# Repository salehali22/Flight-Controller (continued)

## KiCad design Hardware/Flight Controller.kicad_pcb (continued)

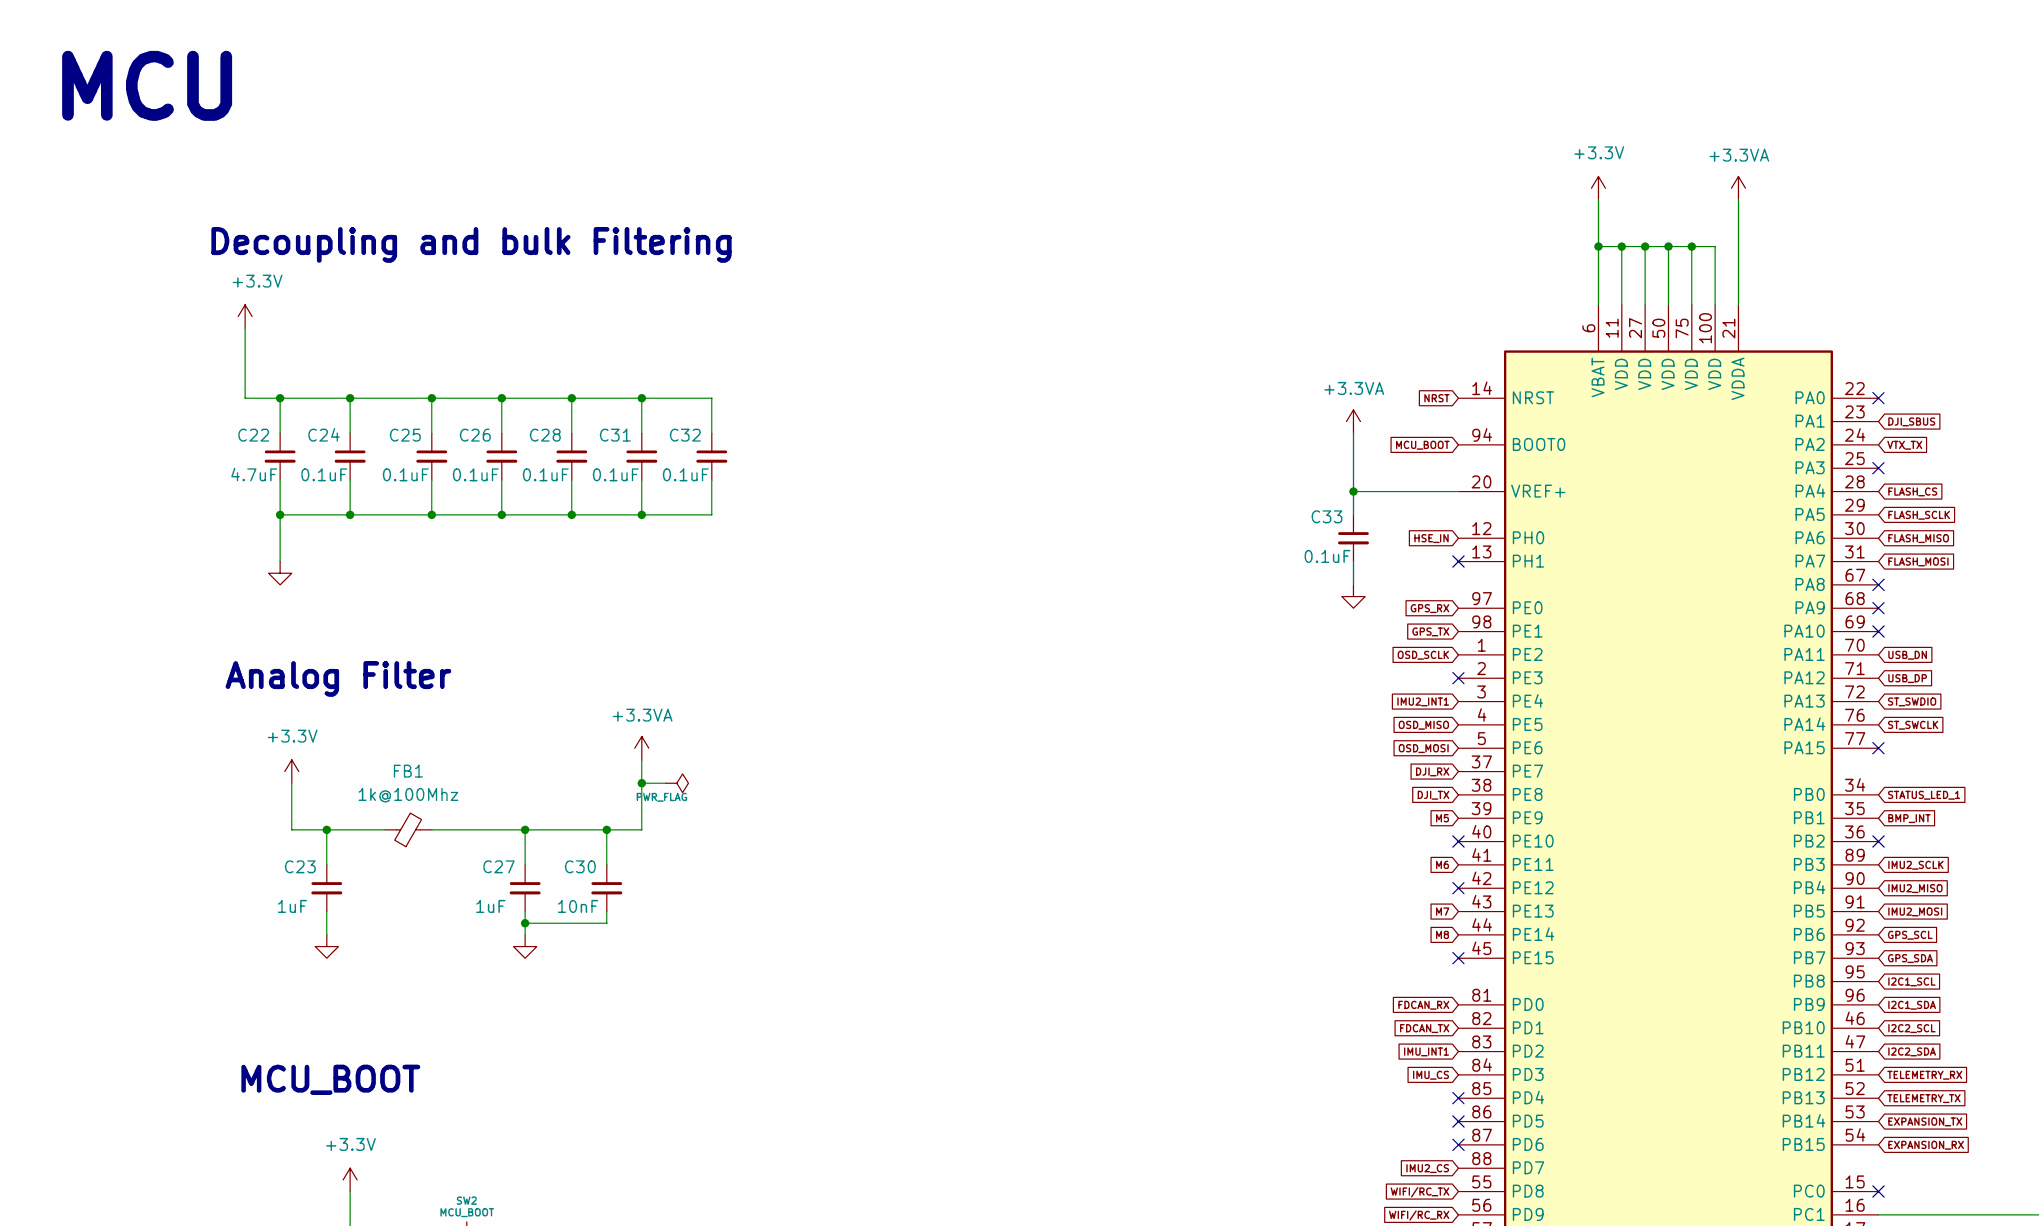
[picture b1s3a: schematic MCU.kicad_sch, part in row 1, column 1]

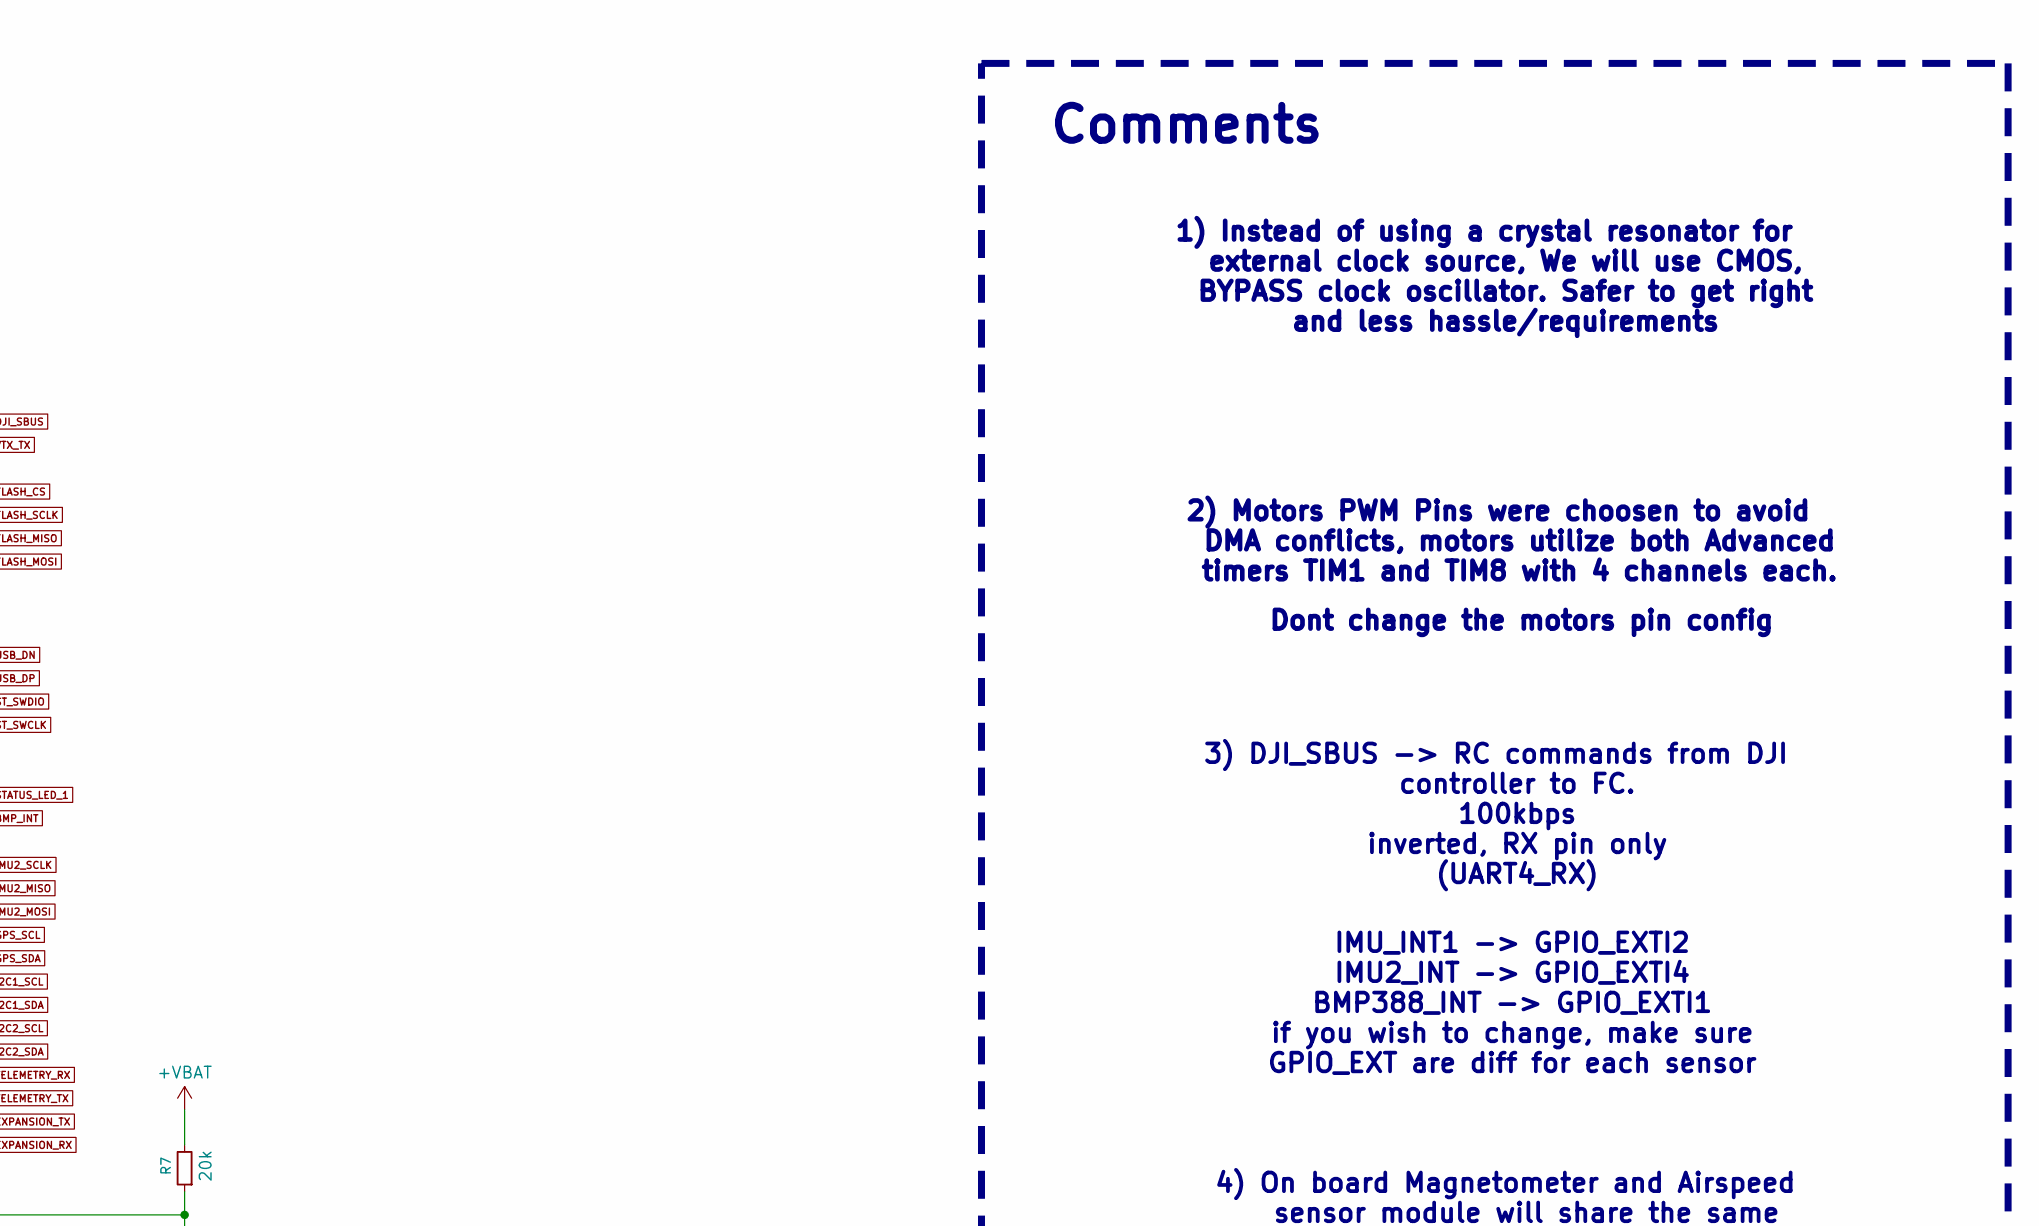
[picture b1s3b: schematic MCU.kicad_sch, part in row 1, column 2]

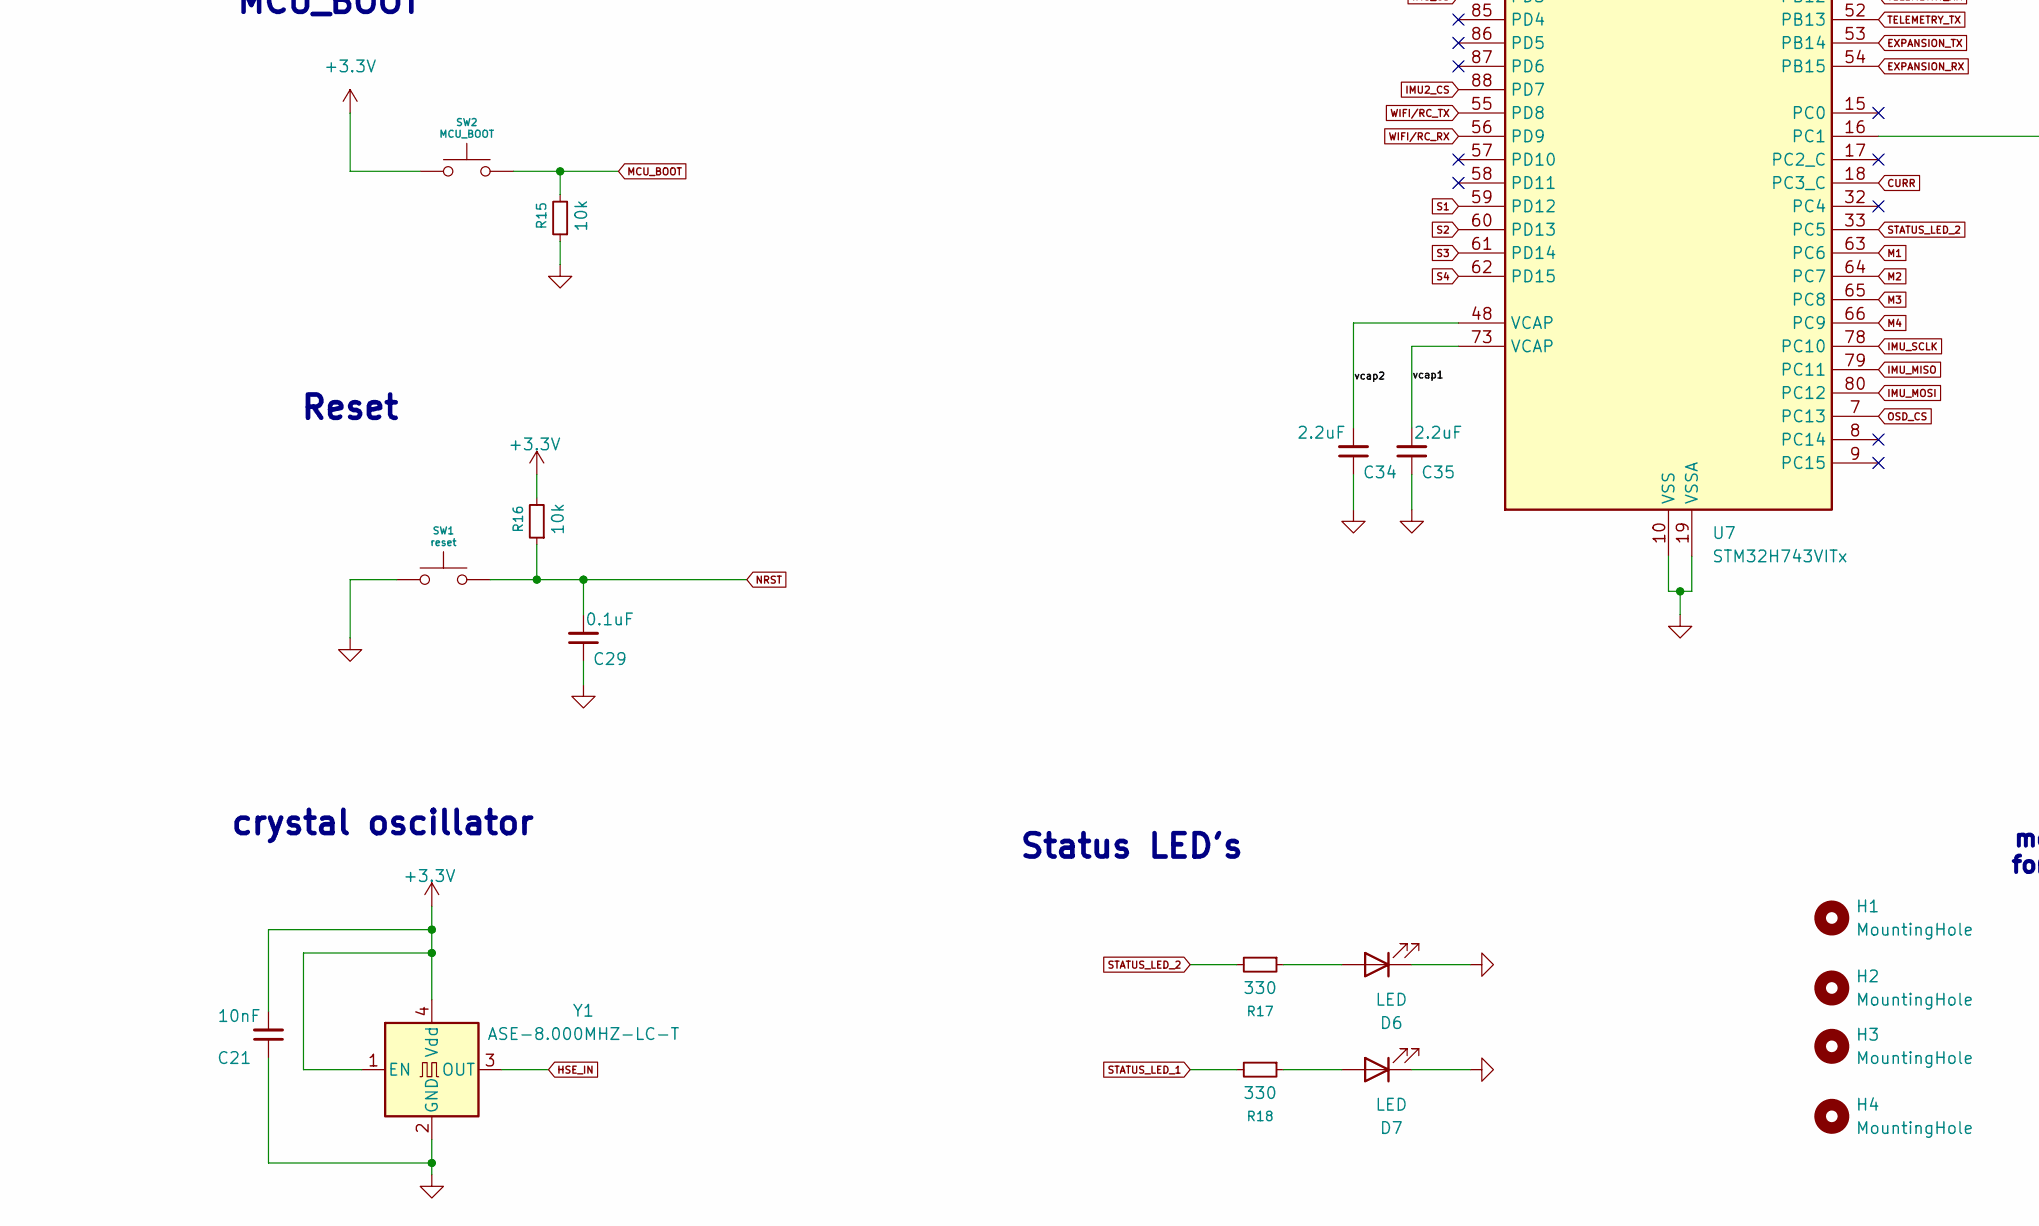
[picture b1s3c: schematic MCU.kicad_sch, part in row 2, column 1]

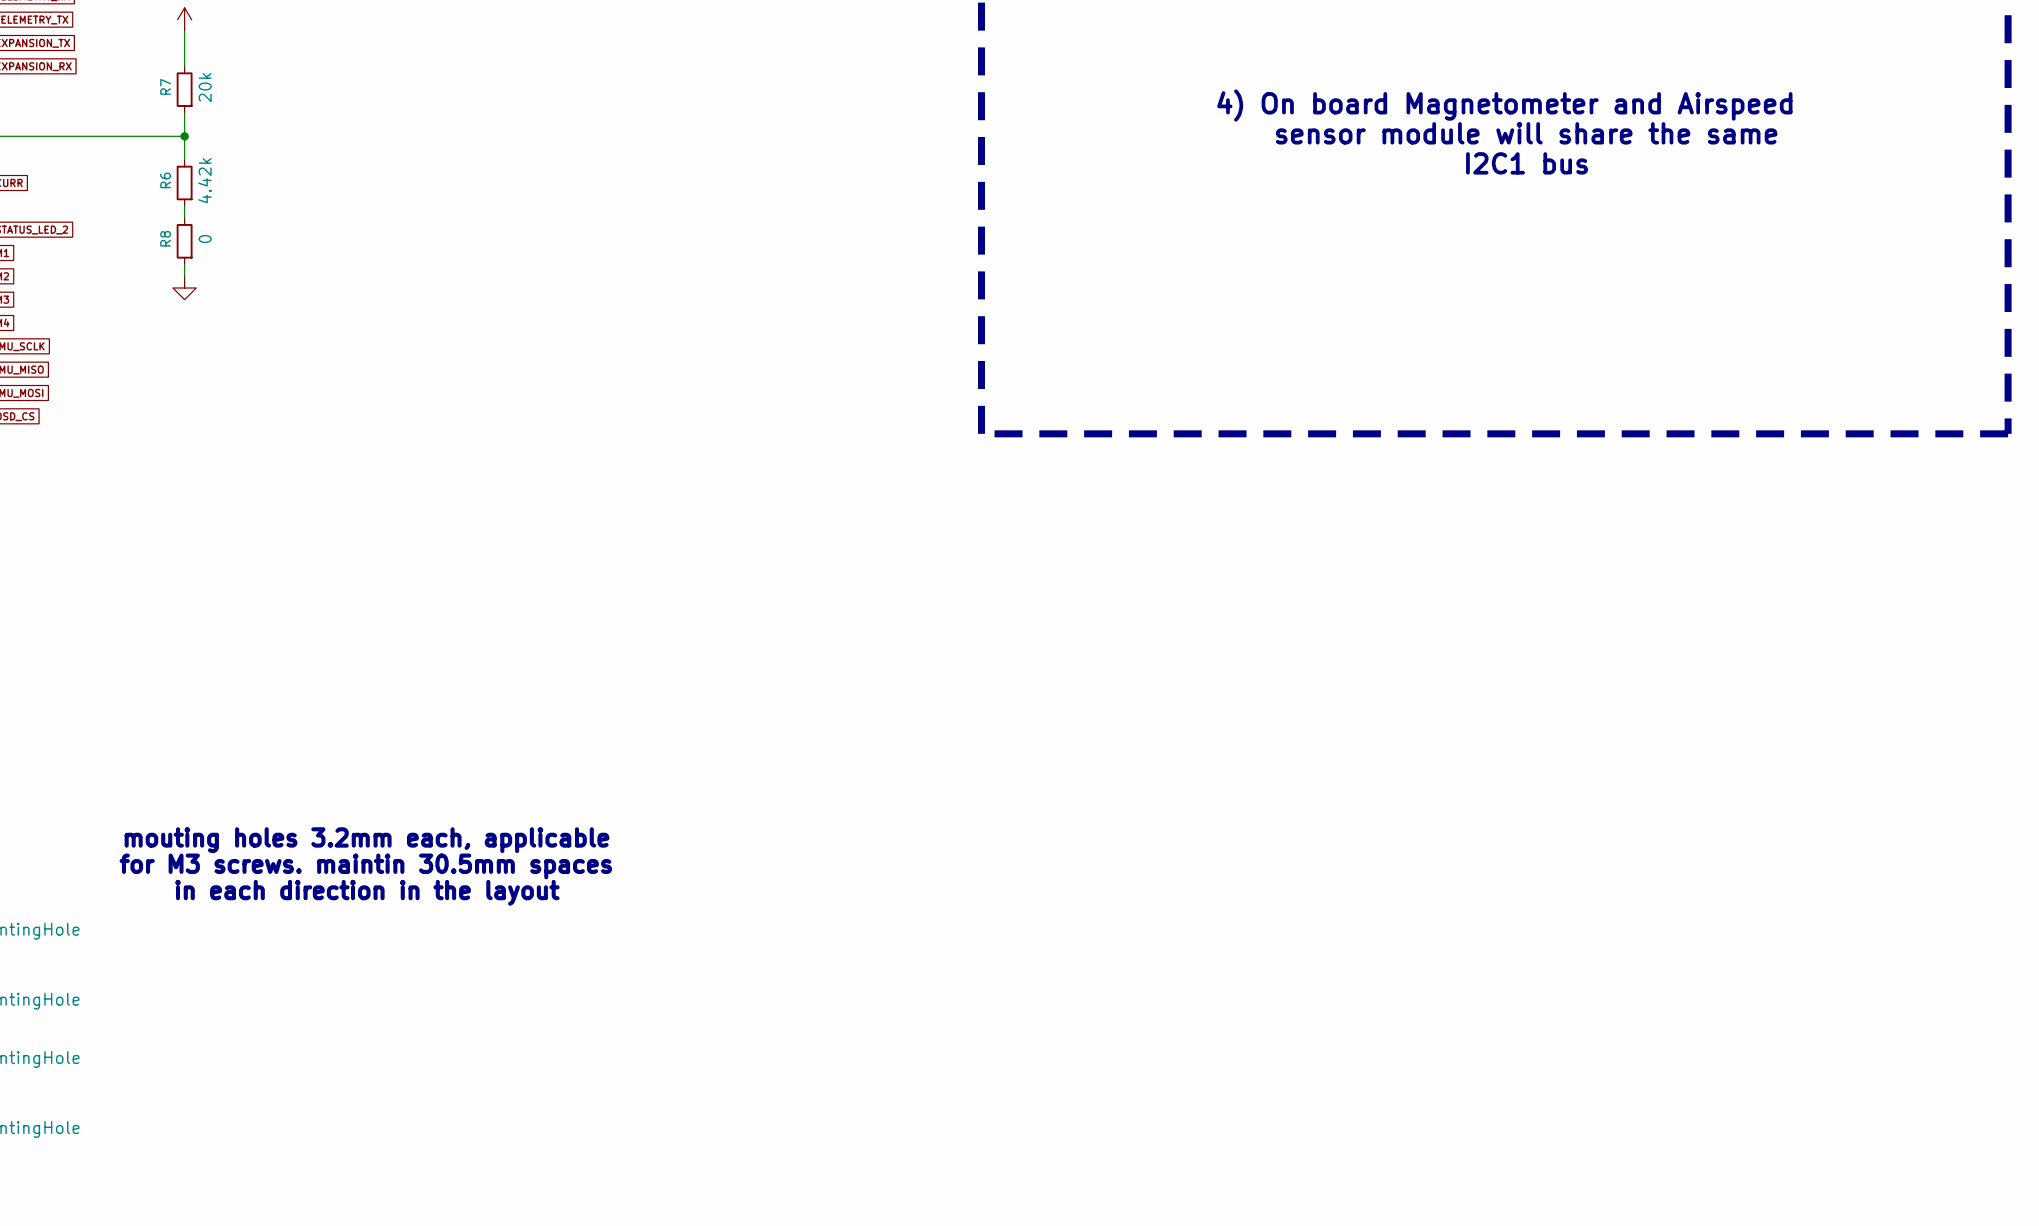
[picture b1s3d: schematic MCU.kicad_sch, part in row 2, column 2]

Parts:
C21: 10nF; C_0603_1608Metric
C22: 4.7uF; C_0603_1608Metric
C23, C27: 1uF; C_0603_1608Metric
C24, C25, C26, C28, C29, C31, C32: 0.1uF; C_0402_1005Metric
C30: 10nF; C_0402_1005Metric
C33: 0.1uF; C_0603_1608Metric
C34, C35: 2.2uF; C_0603_1608Metric
D6, D7: LED; LED_0805_2012Metric
FB1: 1k@100Mhz; L_0603_1608Metric
H1, H2, H3, H4: MountingHole; MountingHole_3.2mm_M3_Pad_Via
R6: 4.42k; R_0402_1005Metric
R7: 20k; R_0402_1005Metric
R8: 0; R_0402_1005Metric
R15, R16: 10k; R_0402_1005Metric
R17, R18: 330; R_0402_1005Metric
SW1: reset; SW_Push_SPST_NO_Alps_SKRK
SW2: MCU_BOOT; SW_Push_SPST_NO_Alps_SKRK
U7: STM32H743VITx; LQFP-100_14x14mm_P0.5mm
Y1: ASE-8.000MHZ-LC-T; Oscillator_SMD_Abracon_ASE-4Pin_3.2x2.5mm

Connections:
+3.3V: C21.2, C22.1, C23.1, C24.1, C25.1, C26.1, C28.1, C31.1, C32.1, FB1.1, R16.2, SW2.1, U7.6 (VBAT), U7.11 (VDD), U7.27 (VDD), U7.50 (VDD), U7.75 (VDD), U7.100 (VDD), Y1.1 (EN), Y1.4 (Vdd); also elsewhere on the board
+3.3VA: C27.1, C30.1, C33.1, FB1.2, U7.20 (VREF+), U7.21 (VDDA)
+VBAT: R7.2; also elsewhere on the board
/MCU/vcap1: C35.2, U7.73 (VCAP)
/MCU/vcap2: C34.2, U7.48 (VCAP)
BMP_INT: U7.35 (PB1); also elsewhere on the board
CURR: U7.18 (PC3_C); also elsewhere on the board
DJI_RX: U7.37 (PE7); also elsewhere on the board
DJI_SBUS: U7.23 (PA1); also elsewhere on the board
DJI_TX: U7.38 (PE8); also elsewhere on the board
EXPANSION_RX: U7.54 (PB15); also elsewhere on the board
EXPANSION_TX: U7.53 (PB14); also elsewhere on the board
FDCAN_RX: U7.81 (PD0); also elsewhere on the board
FDCAN_TX: U7.82 (PD1); also elsewhere on the board
FLASH_CS: U7.28 (PA4); also elsewhere on the board
FLASH_MISO: U7.30 (PA6); also elsewhere on the board
FLASH_MOSI: U7.31 (PA7); also elsewhere on the board
FLASH_SCLK: U7.29 (PA5); also elsewhere on the board
GND: C21.1, C22.2, C23.2, C24.2, C25.2, C26.2, C27.2, C28.2, C29.1, C30.2, C31.2, C32.2, C33.2, C34.1, C35.1, D6.1 (K), D7.1 (K), R8.1, R15.1, SW1.1, U7.10 (VSS), U7.19 (VSSA), U7.26 (VSS), U7.49 (VSS), U7.74 (VSS), U7.99 (VSS), Y1.2 (GND); also elsewhere on the board
GPS_RX: U7.97 (PE0); also elsewhere on the board
GPS_SCL: U7.92 (PB6); also elsewhere on the board
GPS_SDA: U7.93 (PB7); also elsewhere on the board
GPS_TX: U7.98 (PE1); also elsewhere on the board
HSE_IN: U7.12 (PH0), Y1.3 (OUT)
I2C1_SCL: U7.95 (PB8); also elsewhere on the board
I2C1_SDA: U7.96 (PB9); also elsewhere on the board
I2C2_SCL: U7.46 (PB10); also elsewhere on the board
I2C2_SDA: U7.47 (PB11); also elsewhere on the board
IMU2_CS: U7.88 (PD7); also elsewhere on the board
IMU2_INT1: U7.3 (PE4); also elsewhere on the board
IMU2_MISO: U7.90 (PB4); also elsewhere on the board
IMU2_MOSI: U7.91 (PB5); also elsewhere on the board
IMU2_SCLK: U7.89 (PB3); also elsewhere on the board
IMU_CS: U7.84 (PD3); also elsewhere on the board
IMU_INT1: U7.83 (PD2); also elsewhere on the board
IMU_MISO: U7.79 (PC11); also elsewhere on the board
IMU_MOSI: U7.80 (PC12); also elsewhere on the board
IMU_SCLK: U7.78 (PC10); also elsewhere on the board
M1: U7.63 (PC6); also elsewhere on the board
M2: U7.64 (PC7); also elsewhere on the board
M3: U7.65 (PC8); also elsewhere on the board
M4: U7.66 (PC9); also elsewhere on the board
M5: U7.39 (PE9); also elsewhere on the board
M6: U7.41 (PE11); also elsewhere on the board
M7: U7.43 (PE13); also elsewhere on the board
M8: U7.44 (PE14); also elsewhere on the board
MCU_BOOT: R15.2, SW2.2, U7.94 (BOOT0)
NRST: C29.2, R16.1, SW1.2, U7.14 (NRST)
unnamed: D6.2 (A), R17.1
unnamed: D7.2 (A), R18.1
unnamed: R6.1, R8.2
unnamed: R6.2, R7.1, U7.16 (PC1)
OSD_CS: U7.7 (PC13); also elsewhere on the board
OSD_MISO: U7.4 (PE5); also elsewhere on the board
OSD_MOSI: U7.5 (PE6); also elsewhere on the board
OSD_SCLK: U7.1 (PE2); also elsewhere on the board
S1: U7.59 (PD12); also elsewhere on the board
S2: U7.60 (PD13); also elsewhere on the board
S3: U7.61 (PD14); also elsewhere on the board
S4: U7.62 (PD15); also elsewhere on the board
STATUS_LED_1: R18.2, U7.34 (PB0)
STATUS_LED_2: R17.2, U7.33 (PC5)
ST_SWCLK: U7.76 (PA14); also elsewhere on the board
ST_SWDIO: U7.72 (PA13); also elsewhere on the board
TELEMETRY_RX: U7.51 (PB12); also elsewhere on the board
TELEMETRY_TX: U7.52 (PB13); also elsewhere on the board
USB_DN: U7.70 (PA11); also elsewhere on the board
USB_DP: U7.71 (PA12); also elsewhere on the board
VTX_TX: U7.24 (PA2); also elsewhere on the board
WIFI/RC_RX: U7.56 (PD9); also elsewhere on the board
WIFI/RC_TX: U7.55 (PD8); also elsewhere on the board

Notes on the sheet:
Analog Filter
Reset
4) On board Magnetometer and Airspeed sensor module will share the same I2C1 bus
mouting holes 3.2mm each, applicable for M3 screws. maintin 30.5mm spaces in each direction in the layout
1) Instead of using a crystal resonator for external clock source, We will use CMOS, BYPASS clock oscillator. Safer to get right and less hassle/requirements
Comments
MCU
2) Motors PWM Pins were choosen to avoid DMA conflicts, motors utilize both Advanced timers TIM1 and TIM8 with 4 channels each.
3) DJI_SBUS -> RC commands from DJI controller to FC. 100kbps inverted, RX pin only (UART4_RX)
MCU_BOOT
crystal oscillator
IMU_INT1 -> GPIO_EXTI2 IMU2_INT -> GPIO_EXTI4 BMP388_INT -> GPIO_EXTI1 if you wish to change, make sure GPIO_EXT are diff for each sensor
Dont change the motors pin config
Decoupling and bulk Filtering
Status LED's

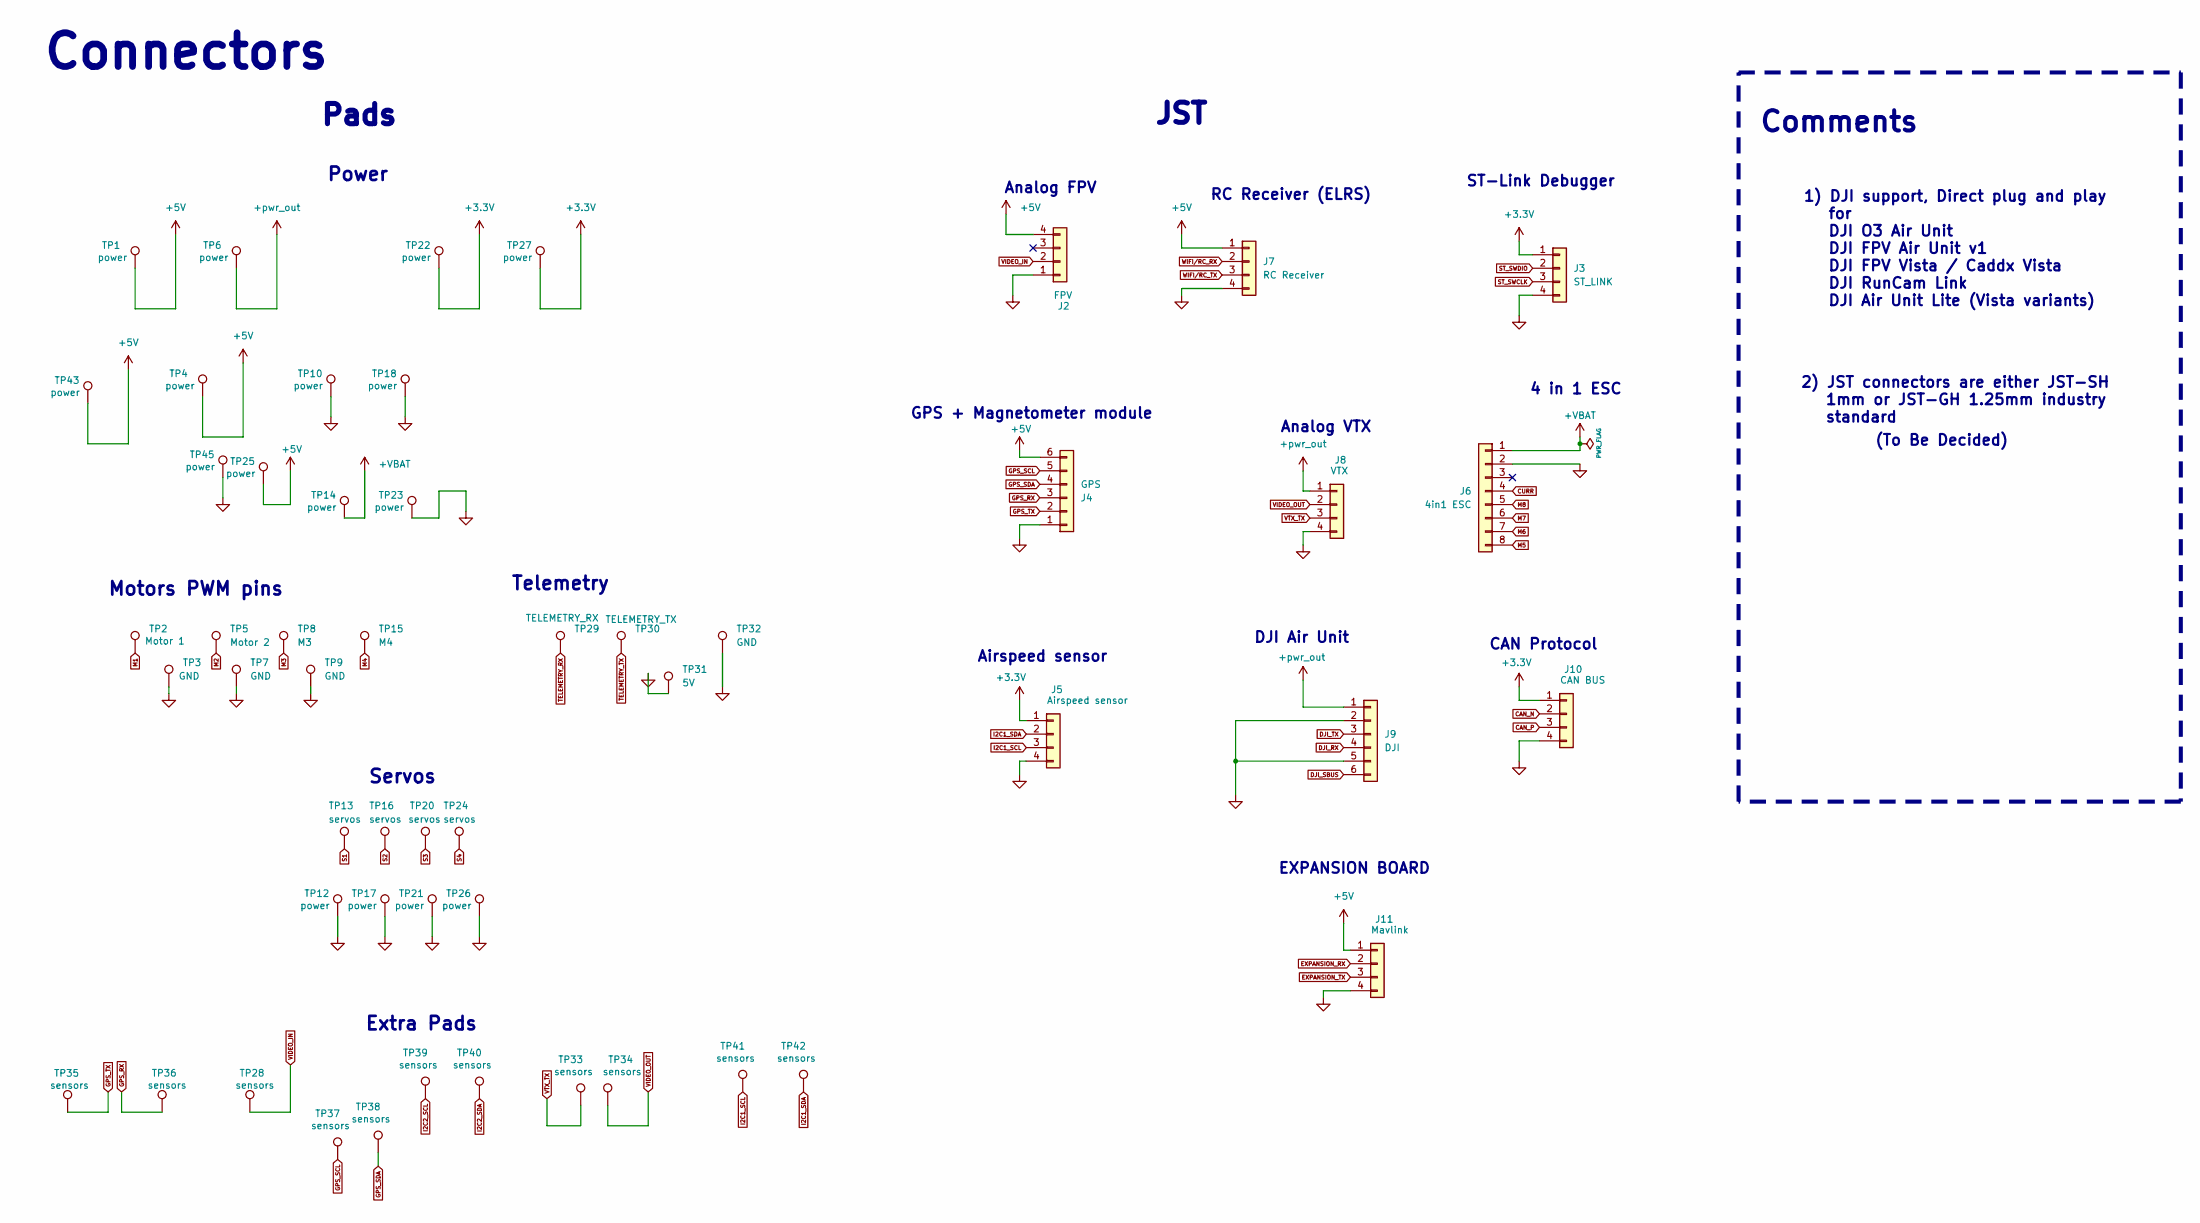
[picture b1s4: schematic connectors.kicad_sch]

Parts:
J2: FPV; CONN-SMD_4P-P1.00_SM04B-SRSS-TB-LF-SN
J3: ST_LINK; CONN-SMD_4P-P1.00_SM04B-SRSS-TB-LF-SN
J4: GPS; JST_SH_SM06B-SRSS-TB_1x06-1MP_P1.00mm_Horizontal
J5: Airspeed sensor; CONN-SMD_4P-P1.00_SM04B-SRSS-TB-LF-SN
J6: 4in1 ESC; JST_SH_SM08B-SRSS-TB_1x08-1MP_P1.00mm_Horizontal
J7: RC Receiver; CONN-SMD_4P-P1.00_SM04B-SRSS-TB-LF-SN
J8: VTX; CONN-SMD_4P-P1.00_SM04B-SRSS-TB-LF-SN
J9: DJI; JST_SH_SM06B-SRSS-TB_1x06-1MP_P1.00mm_Horizontal
J10: CAN BUS; CONN-SMD_4P-P1.00_SM04B-SRSS-TB-LF-SN
J11: Mavlink; CONN-SMD_4P-P1.00_SM04B-SRSS-TB-LF-SN
TP1, TP4, TP6, TP10, TP12, TP17, TP18, TP21, TP22, TP25, TP26, TP27, TP43, TP45: power; Solderpad
TP2: Motor 1; Solderpad
TP3, TP7, TP9, TP32: GND; Solderpad
TP5: Motor 2; Solderpad
TP8: M3; Solderpad
TP13, TP16, TP20, TP24: servos; Solderpad
TP14, TP23: power; BAT pad
TP15: M4; Solderpad
TP28, TP33, TP34, TP35, TP36, TP37, TP38, TP39, TP40, TP41, TP42: sensors; Solderpad
TP29: TELEMETRY_RX; Solderpad
TP30: TELEMETRY_TX; Solderpad
TP31: 5V; Solderpad

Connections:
+3.3V: J3.1, J5.1, J10.1, TP22.1 (1_1), TP27.1 (1_1); also elsewhere on the board
+5V: J2.4, J4.6, J7.1, J11.1, TP1.1 (1_1), TP4.1 (1_1), TP25.1 (1_1), TP43.1 (1_1); also elsewhere on the board
+VBAT: J6.1, TP14.1 (1_1); also elsewhere on the board
+pwr_out: J8.1, J9.1, TP6.1 (1_1); also elsewhere on the board
CAN_N: J10.2; also elsewhere on the board
CAN_P: J10.3; also elsewhere on the board
CURR: J6.4; also elsewhere on the board
DJI_RX: J9.4; also elsewhere on the board
DJI_SBUS: J9.6; also elsewhere on the board
DJI_TX: J9.3; also elsewhere on the board
EXPANSION_RX: J11.2; also elsewhere on the board
EXPANSION_TX: J11.3; also elsewhere on the board
GND: J2.1, J3.4, J4.1, J5.4, J6.2, J7.4, J8.4, J9.2, J9.5, J10.4, J11.4, TP3.1 (1_1), TP7.1 (1_1), TP9.1 (1_1), TP10.1 (1_1), TP12.1 (1_1), TP17.1 (1_1), TP18.1 (1_1), TP21.1 (1_1), TP23.1 (1_1), TP26.1 (1_1), TP31.1 (1_1), TP32.1 (1_1), TP45.1 (1_1); also elsewhere on the board
GPS_RX: J4.3, TP36.1 (1_1); also elsewhere on the board
GPS_SCL: J4.5, TP37.1 (1_1); also elsewhere on the board
GPS_SDA: J4.4, TP38.1 (1_1); also elsewhere on the board
GPS_TX: J4.2, TP35.1 (1_1); also elsewhere on the board
I2C1_SCL: J5.3, TP41.1 (1_1); also elsewhere on the board
I2C1_SDA: J5.2, TP42.1 (1_1); also elsewhere on the board
I2C2_SCL: TP39.1 (1_1); also elsewhere on the board
I2C2_SDA: TP40.1 (1_1); also elsewhere on the board
M1: TP2.1 (1_1); also elsewhere on the board
M2: TP5.1 (1_1); also elsewhere on the board
M3: TP8.1 (1_1); also elsewhere on the board
M4: TP15.1 (1_1); also elsewhere on the board
M5: J6.8; also elsewhere on the board
M6: J6.7; also elsewhere on the board
M7: J6.6; also elsewhere on the board
M8: J6.5; also elsewhere on the board
S1: TP13.1 (1_1); also elsewhere on the board
S2: TP16.1 (1_1); also elsewhere on the board
S3: TP20.1 (1_1); also elsewhere on the board
S4: TP24.1 (1_1); also elsewhere on the board
ST_SWCLK: J3.3; also elsewhere on the board
ST_SWDIO: J3.2; also elsewhere on the board
TELEMETRY_RX: TP29.1 (1_1); also elsewhere on the board
TELEMETRY_TX: TP30.1 (1_1); also elsewhere on the board
VIDEO_IN: J2.2, TP28.1 (1_1); also elsewhere on the board
VIDEO_OUT: J8.2, TP34.1 (1_1); also elsewhere on the board
VTX_TX: J8.3, TP33.1 (1_1); also elsewhere on the board
WIFI/RC_RX: J7.2; also elsewhere on the board
WIFI/RC_TX: J7.3; also elsewhere on the board

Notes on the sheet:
Servos
JST
RC Receiver (ELRS)
ST-Link Debugger
GPS + Magnetometer module
4 in 1 ESC
Power
Telemetry
CAN Protocol
EXPANSION BOARD
Comments
Airspeed sensor
2) JST connectors are either JST-SH 1mm or JST-GH 1.25mm industry standard
1) DJI support, Direct plug and play for DJI O3 Air Unit DJI FPV Air Unit v1 DJI FPV Vista / Caddx Vista DJI RunCam Link DJI Air Unit Lite (Vista variants)
Extra Pads
Analog VTX
DJI Air Unit
(To Be Decided)
Connectors
Pads
Analog FPV
Motors PWM pins
